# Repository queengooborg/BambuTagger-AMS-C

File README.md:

#  BambuTagger-AMS-C

Multi-spool NFC tag reader for Bambu Lab printers. Reads 4 Bambu Lab filament spool tags via RC522, displays live printer AMS tray data over MQTT, and sends RFID tag data to the printer/BMCU. Fully configurable via web interface with automatic AP fallback and OTA firmware updates.

Supported Tag Formats:

| Tag Type                  | Format            |
| ------------------------- | ----------------- |
| **Bambu Lab**             | MIFARE Classic 1K |
| **SpoolEase**             | NTAG, NDEF URI    |
| **OpenSpool**             | NTAG, NDEF JSON   |
| **OpenTag3D** (v1 and v2) | NTAG, MIME binary |

---

## Features

| Category           | Details                                                                                                         |
| ------------------ | --------------------------------------------------------------------------------------------------------------- |
| **RFID**           | 4x RC522 on shared SPI bus; MIFARE Classic 1K (Bambu Lab) + NTAG (SpoolEase/OpenTag3D/OpenSpool) auto-detection |
| **Key derivation** | HKDF-SHA256 with Bambu Lab salt — no hardcoded keys                                                             |
| **Tag parsers**    | OpenTag3D MIME binary, OpenSpool JSON, SpoolEase NDEF URI, nested NDEF recursion                                |
| **Live AMS sync**  | Reads tray data (material, color, type) from printer over MQTT                                                  |
| **BMCU support**   | Sends `ams_filament_setting` with correct `tray_type`, `tray_color`, `nozzle_temp_min/max`                      |
| **TFT display**    | 240×240 1.3" ST7789VW with boot splash, live AMS tray data, OTA progress, BME280 temp/humidity                  |
| **LEDs**           | 4x WS2812 addressable LEDs with per-slot color from printer AMS tray data                                       |
| **Web UI**         | 3-tab SPA: Status (merged slots + color swatches), Printer Config, WiFi Config                                  |
| **MQTT bridge**    | Subscribes to printer status, publishes `ams_filament_setting` commands                                         |
| **WiFi**           | Auto-STA on boot; AP fallback `192.168.4.1` with captive portal                                                 |
| **OTA updates**    | One-click firmware update from GitHub Releases with TFT progress bar                                            |
| **CI/CD**          | GitHub Actions: build on commit, release on version tags                                                        |

---

## Hardware

This build assumes you have a basic level of microprocessor and breadboard/soldering experience.

### Bill of Materials

There are two options for ESP32 boards: the ESP-WROOM-32 Dev board, or the ESP32-S3-DevKitC-1.

#### ESP-WROOM-32

This is the original board.

| Component            | Required | Notes                                      | Buy/Download/Get                                                                                                                |
| -------------------- | -------- | ------------------------------------------ | ------------------------------------------------------------------------------------------------------------------------------- |
| **ESP32** Dev Module | **Yes**  | Base board                                 | https://de.aliexpress.com/item/1005006589341221.html                                                                            |
| Custom **PCB**       | Optional | DIY PCB from JLPCB (use PCB v1.2 or newer) | https://oshwlab.com/bambutagger/project_hdkkdlsn                                                                                |
| 3D-Printed **Case**  | Optional |                                            | For [AMS](./3d-prints/ESP-WROOM-32/BambuTagger-AMS.3mf)<br /> For [AMS 2 Pro](./3d-prints/ESP-WROOM-32/BambuTagger-AMS2Pro.3mf) |

#### ESP32-S3-DevKitC-1

| Component            | Required | Notes                            | Buy/Download/Get                         |
| -------------------- | -------- | -------------------------------- | ---------------------------------------- |
| **ESP32** Dev Module | **Yes**  | Base board                       |                                          |
| Custom **PCB**       | Optional | DIY PCB designed by @Digitalpunk | [Gerber Files](./PCB/ESP32-S3-DevKitC-1) |

#### Common Components

| Component                           | Required        | Notes                          | Buy/Download/Get                                      |
| ----------------------------------- | --------------- | ------------------------------ | ----------------------------------------------------- |
| **100µF Capacitor**                 | **Yes**         | Regulates power for components |                                                       |
| **4x RC522** RFID/NFC Readers       | **Yes**         | SPI interface, shared bus      | https://de.aliexpress.com/item/1005006233005745.html  |
| **240×240 1.3" TFT**                | **Yes**         | ST7789VW SPI Display           | https://www.aliexpress.com/item/1005007094147766.html |
| **4x WS2812** Addressable LEDs      | Optional        | Daisy-chained, single data pin | https://de.aliexpress.com/item/32560280169.html       |
| **BME280** 3.3V Sensor              | Optional        | Temperature/Humidity, I2C      | https://de.aliexpress.com/item/1005006824236173.html  |
| **4x JST-XH 7-Pin** Connector+Cable | With Custom PCB | For PCB connections to RC522s  |                                                       |

### Wiring / Pin Assignments

If you are not using the custom PCB, you can manually wire all the components.

Connect the ESP32 to a 5V power input, either via the USB port or via the VCC/Vin pin.

The WS2812 LED must also be powered by 5V. If the ESP32 is powered via the USB port, the VCC/Vin pin becomes a 5V output, and can be used to power the LEDs. On some boards, you may need to short two pads (usually labeled VIN->VOUT) via soldering.

Connect the 100µF capacitor from the 3.3V to the ground. This capacitor helps regulate power and prevents back-powering the RC522 readers.

All other components will be powered by the 3.3V pin on the ESP32 board.

| Function                    | ESP-WROOM-32 | ESP32-S3-DevKitC-1 |
| --------------------------- | ------------ | ------------------ |
| **RC522 SPI MOSI (Shared)** | 23           | 11                 |
| **RC522 SPI MISO (Shared)** | 19           | 13                 |
| **RC522 SPI SCK (Shared)**  | 18           | 12                 |
| **RC522 #1 SS (SDA)**       | 13           | 4                  |
| **RC522 #1 RST**            | 26           | 15                 |
| **RC522 #2 SS (SDA)**       | 12           | 5                  |
| **RC522 #2 RST**            | 25           | 16                 |
| **RC522 #3 SS (SDA)**       | 14           | 6                  |
| **RC522 #3 RST**            | 33           | 17                 |
| **RC522 #4 SS (SDA)**       | 27           | 7                  |
| **RC522 #4 RST**            | 32           | 18                 |
| **TFT SDA (MOSI)**          | 17           | 35                 |
| **TFT SCL (SCK)**           | 16           | 36                 |
| **TFT DC**                  | 4            | 37                 |
| **TFT RES**                 | 5            | 0                  |
| **TFT BLK**                 | 2            | 45                 |
| **WS2812 Data**             | 15           | 14                 |
| **BME280 SDA**              | 21           | 48                 |
| **BME280 SCL**              | 22           | 47                 |

---

## Firmware

### Flashing a Release

The easiest way to flash the board firmware is to use a web flashing utility like [ESPFlasher.app](https://espflasher.app/). Simply download the appropriate `firmware_merged.bin` from the [releases](https://github.com/queengooborg/BambuTagger-AMS-C/releases) page and upload it to the flashing utility.

- ESP-WROOM-32 / ESP32 Dev Module - `esp32dev-firmware_merged.bin`
- ESP32-S3-DevKitC-1 - `esp32-s3-devkitc-1-firmware_merged.bin`

Alternatively, if you have `esptool` set up locally, you may run the following command:

- ESP-WROOM-32 / ESP32 Dev Module - `esptool write-flash 0x0 esp32dev-firmware_merged.bin`
- ESP32-S3-DevKitC-1 - `esptool --chip esp32s3 write-flash 0x0 esp32-s3-devkitc-1-firmware_merged.bin`

### Building from Source

To build from source, you may either use Visual Studio Code or run commands in the terminal. The following sections will cover setup for running commands in the terminal.

#### Initial Setup

To setup the local development environment, you can either use Visual Studio Code, or run the `./setup.sh` command. The command will create a Python virtual environment, using the virtualenv manager if one is available, and install dependencies.

> [!NOTE]
> To reactivate the virtualenv at a later time (if you don't have a virtualenv manager), simply run:
>
> ```sh
> source .venv/bin/activate
> ```

#### Build and Upload

```sh
# ESP32-WROOM / ESP32 Dev Module
pio run -e esp32-ams-c
pio run -e esp32-ams-c -t upload

# ESP32-S3-DevKitC-1
pio run -e esp32-s3-devkitc-1
pio run -e esp32-s3-devkitc-1 -t upload
```

---

## How to Use

### Initial Setup

Once the firmware has been flashed for the first time, the ESP32 will initialize and create its own WiFi access point called "BambuTagger-AMS". Connect to the WiFi network to access the web-based configuration panel.

> [!NOTE]
> The configuration panel should automatically appear as a captive portal. If it does not, manually go to it by going to `http://192.168.4.1` in your browser.

Configure your WiFi network first by typing in the SSID name and password, then click "Save WiFi Settings". The ESP32 will reboot automatically. If the network configuration succeeded, you can now switch to your primary WiFi. If it did not, the WiFi access point will reinitialize, allowing you to reconnect.

Once WiFi configuration is completed, reconnect to your device by navigating to `[Device Name].local` (default: `BambuTagger-AMS.local`) or via the IP address displayed on the TFT screen.

Enter in your printer settings on the printer config page, including the IP, serial number and access code.

> [!IMPORTANT]
> Your printer MUST be in LAN Only Mode and Developer Mode. The printer will refuse all connections otherwise.

### Using with Printer

The project is designed with the intent of placing a reader at each AMS slot, similar to how the existing readers are placed. With each reader placed, tag scanning will happen automatically as filament is loaded normally.

--

## Technical Details

### WiFi & Connectivity

#### AP Mode

| Scenario                     | Behavior                                |
| ---------------------------- | --------------------------------------- |
| No WiFi configured           | Opens AP immediately                    |
| WiFi connection fails        | Opens AP after 15 seconds               |
| AP active, credentials exist | Retries STA connection every 30 seconds |
| STA connects while AP active | Closes AP, switches to normal mode      |

**AP Details:**

- **SSID**: Device name (default: `BambuTagger-AMS`)
- **Security**: Open (no password)
- **IP**: `192.168.4.1`
- **Captive portal**: DNS redirects all domains to the config page

#### SSID Mode

When the ESP32 module is connected to an existing network, the IP address will display on the TFT screen. Alternatively, you may navigate to `[Device Name].local` (default: `BambuTagger-AMS.local`).

---

### Web Interface

Open a browser to the ESP32's IP (shown on TFT), `[Device Name].local`, or `http://192.168.4.1` (in AP mode).

| Tab                | Description                                                                                        |
| ------------------ | -------------------------------------------------------------------------------------------------- |
| **Status**         | Merged slot status with AMS data + scanned tag data, color swatches, printer AMS cards, OTA button |
| **Printer Config** | Printer IP, Port (8883), Access Code, Serial Number, AMS Unit selector (A/B/C/D), MQTT settings    |
| **WiFi Config**    | SSID, Password, Device Name                                                                        |

---

### TFT Display (240×240 1.3" ST7789VW)

The TFT display has two modes:

```
┌─────────────────────────────────┐
│ Device Name               WiFi  │  ← status bar (white bg)
├─────────────────────────────────┤
│    1       2                    │
│ ┌─────┐ ┌─────┐ ┌─────┐ ┌─────┐ │  ← color swatch + percentage
│ │  P  │ │     │ │     │ │     │ │
│ │  L  │ │     │ │     │ │     │ │
│ │  A  │ │     │ │     │ │     │ │
│ │     │ │     │ │     │ │     │ │
│ │     │ │     │ │     │ │     │ │
│ └─────┘ └─────┘ └─────┘ └─────┘ │
│                                 │
│  100%                           │
├─────────────────────────────────┤
│ 22C           45%               │  ← temperature, humidity
│ MQTT:OK                  PTR:OK │  ← status line
└─────────────────────────────────┘
```

```
┌─────────────────────────────────┐
│ Device Name               WiFi  │  ← status bar (white bg)
├─────────────────────────────────┤
│ 1: PLA     [■] #C0C0C0FF  100%  │  ← color swatch + percentage
│ 2: empty                        │
│ 3: empty                        │
│ 4: empty                        │
├─────────────────────────────────┤
│ 22C           45%               │  ← temperature, humidity
│ MQTT:OK                  PTR:OK │  ← status line
└─────────────────────────────────┘
```

OTA progress shown on TFT with header/footer preserved:  
"OTA Update" → "Downloading..." → "Flashing... 45%" → auto-reboot

---

### Printer Communication

#### Subscribe

- **Topic**: `device/<serial>/report`
- **Data**: `push_status` (periodic, ~3KB), `get_version` responses

#### Publish

- **Topic**: `device/<serial>/request`

**`ams_filament_setting`** structure:

```json
{
  "print": {
    "sequence_id": "0",
    "command": "ams_filament_setting",
    "ams_id": 0,
    "tray_id": 0,
    "tray_info_idx": "GFA00",
    "tray_color": "RRGGBBFF",
    "nozzle_temp_min": 190,
    "nozzle_temp_max": 230,
    "tray_type": "PLA"
  }
}
```

- `tray_type` derived from filament index prefix (GFA→PLA, GFG→PETG, etc.)
- `tray_color` forced to RRGGBBFF format
- `nozzle_temp_min/max` from tag block 6

---

### Tag Format & Reading

The following tag types are supported:

| Tag Type                  | Format            | Example                                              |
| ------------------------- | ----------------- | ---------------------------------------------------- |
| **Bambu Lab**             | MIFARE Classic 1K | `Bambu - PLA · C12E1FFF · 1000g/1000g`               |
| **SpoolEase**             | NTAG, NDEF URI    | `SpoolEase - PLA · 000000FF · 1000g/1036g`           |
| **OpenSpool**             | NTAG, NDEF JSON   | `OpenSpool - ASA-AF · F078B4FF · 1000g/1000g`        |
| **OpenTag3D** (v1 and v2) | NTAG, MIME binary | `OpenTag3D v2.003 - ASA-AF · F078B4FF · 1000g/1000g` |

#### Bambu Lab (MIFARE Classic 1K)

| Block | Content                                              |
| ----- | ---------------------------------------------------- |
| 0     | UID (4 bytes)                                        |
| 1     | Variant ID + Material index (e.g. "GFA00")           |
| 2     | Filament type short name                             |
| 4     | Detailed type string (e.g. "PLA Basic")              |
| 5     | RGBA color (bytes 0-3) + spool weight LE (bytes 4-5) |
| 6     | Nozzle temps (bytes 8-11 LE)                         |

#### SpoolEase (NTAG, NDEF URI)

URL format: `https://tag.spoolease.io/S1/?TG=...&M=PLA&CC=000000FF&SC=GFL99&WL=1000&WE=179&WF=1215&NN=190&NX=240`

| Param | Field            | Description                         |
| ----- | ---------------- | ----------------------------------- |
| `M=`  | display type     | e.g. "PLA", "PETG"                  |
| `SC=` | `materialType`   | Bambu index for MQTT (e.g. "GFL99") |
| `CC=` | `colorHex`       | RGBA hex (e.g. "000000FF")          |
| `B=`  | `manufacturer`   | Brand name (e.g. "Jayo")            |
| `WL=` | `remainingGrams` | Remaining filament weight           |
| `WE=` | empty spool      | Empty spool weight                  |
| `WF=` | full spool       | `totalGrams = WF - WE`              |
| `NN=` | `nozzleTempMin`  | Min nozzle temp °C                  |
| `NX=` | `nozzleTempMax`  | Max nozzle temp °C                  |

#### OpenTag3D (NTAG, MIME binary)

The OpenTag3D spec can be read on [their website](https://opentag3d.info/spec).

### Authentication & Reading

- **Tag auto-detect**: SAK-based type detection (MIFARE 1K vs NTAG)
- **HKDF-SHA256** derives 16 per-sector Key A/B from 4-byte UID
- Bambu KDF salt/info vectors from reverse-engineered firmware
- Falls back to default key `0xFF...FF` for blank sectors
- Failed auth re-wakes tag via antenna power-cycle
- Dead readers auto-skipped (version register 0x92/0x91/0xB2 check)
- SPI: 1 MHz via `MFRC522_SPI`
- NTAG: page-level reads (page+=4, 4 pages per MIFARE_Read)

### Filament Type Mapping

| Prefix       | Type |
| ------------ | ---- |
| GFA-GFE, GFL | PLA  |
| GFG          | PETG |
| GFH, GFI     | ABS  |
| GFJ          | ASA  |
| GFK          | TPU  |

---

### OTA Updates

- **Button**: "Update Firmware" on Status page (shows "Update to vX.Y.Z" or "up to date")
- **Overlay**: full-screen progress overlay with spinner, status text, progress bar
- **Endpoint**: `POST /api/ota` triggers update, `GET /api/ota-check` checks for newer version
- Downloads latest `.ino.bin` from GitHub Releases, flashes via `Update.h`
- 3 retry attempts with 5s stall detection, fresh HTTP client per attempt
- TFT shows "Checking version..." → "Downloading..." → "Flashing..." with percentage
- Device auto-reboots after successful flash, web UI auto-reloads

---

### Configuration Defaults

| Setting              | Default         |
| -------------------- | --------------- |
| WiFi SSID            | (empty)         |
| WiFi Password        | (empty)         |
| Device Name          | BambuTagger-AMS |
| Printer IP           | 192.168.1.100   |
| Printer Port         | 8883            |
| Access Code          | (empty)         |
| Printer Serial       | (empty)         |
| AMS Unit             | A (0)           |
| MQTT Enabled         | Yes             |
| MQTT TLS             | No              |
| MQTT Update Interval | 3000 ms         |
| RFID Poll Interval   | 100 ms          |
| Firmware Version     | 1.0.8           |

---

## Credits & References

- [RFID-Tag-Guide](https://github.com/Bambu-Research-Group/RFID-Tag-Guide)
- Display library: [Adafruit ST7735/ST7789](https://github.com/adafruit/Adafruit-ST7735-Library)
- RFID library: [MFRC522-spi-i2c-uart-async](https://github.com/miguelbalboa/rfid)
- OpenTag3D spec: [opentag3d.info](https://opentag3d.info)

---

## License

This project is licened under AGPLv3.
This project is provided as-is for personal and educational use.  
Bambu Lab trademarks and spool tag data formats are the property of Bambu Lab.

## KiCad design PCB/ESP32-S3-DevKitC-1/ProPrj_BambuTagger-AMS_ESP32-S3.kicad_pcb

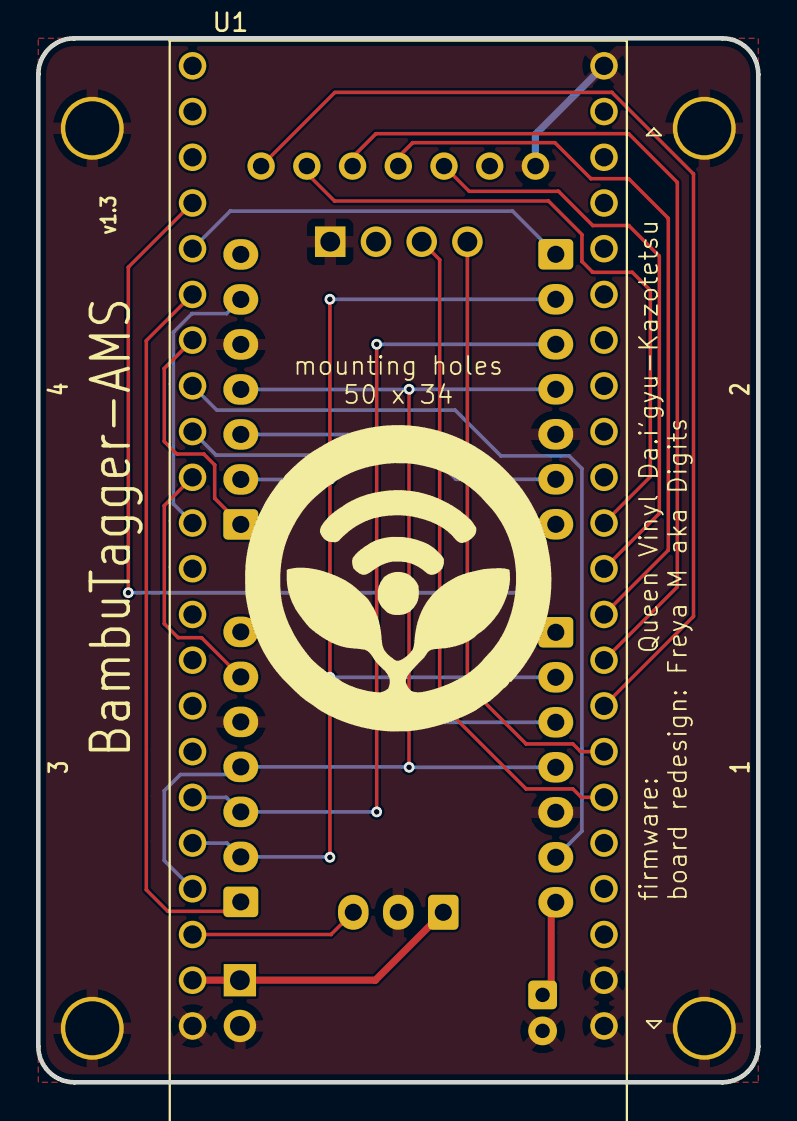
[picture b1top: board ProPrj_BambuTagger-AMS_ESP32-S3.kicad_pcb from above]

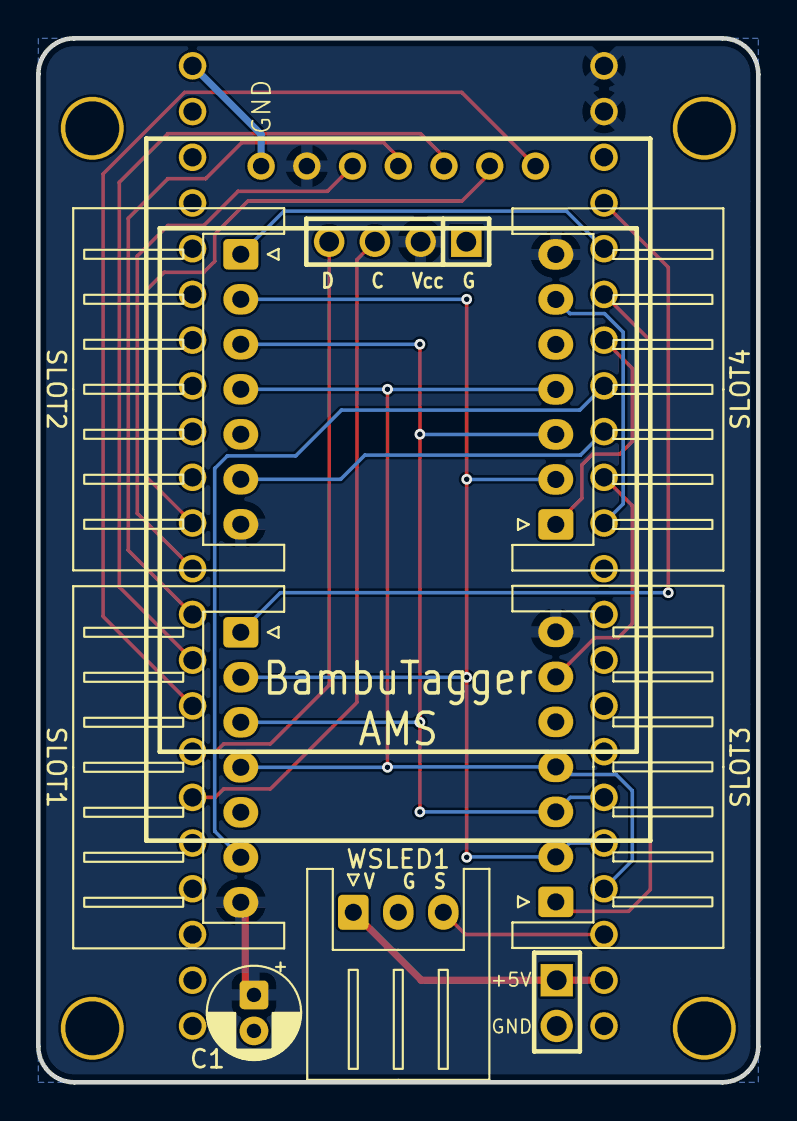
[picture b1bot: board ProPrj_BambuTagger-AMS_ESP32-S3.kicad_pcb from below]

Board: 2 copper layers, 40.0 x 58.0 mm, 10 parts (9 on the bottom side), 22 nets.

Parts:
5V: HDR-TH_2P-P2.54-H-M-W10.4
C1: 100uF; CP_Radial_D5.0mm_P2.00mm
SENSOR: HDR-TH_4P-P2.54-V-M
SLOT1, SLOT2, SLOT3, SLOT4: ZX-XH2.54-7PWZ; JST_XH_S7B-XH-A_1x07_P2.50mm_Horizontal
TFT: 240X240 1.3 TFT SPI DISPLAY
U1: ESP32-S3-DEVKITC-1U-N8R8; MODULE_ESP32-S3-DEVKITC-1U-N8R8
WSLED1: ZX-XH2.54-3PWZ; JST_XH_S3B-XH-A_1x03_P2.50mm_Horizontal

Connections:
3_3V: C1.1, SENSOR.2, SLOT1.7, SLOT2.7, SLOT3.7, SLOT4.7, TFT.6, U1.J1_1 (3V3), U1.J1_2 (3V3)
BLK: TFT.1, U1.J3_15 (GPIO45)
CS1: SLOT1.1, U1.J1_4 (GPIO4)
CS2: SLOT2.1, U1.J1_5 (GPIO5)
CS3: SLOT3.1, U1.J1_6 (GPIO6)
CS4: SLOT4.1, U1.J1_7 (GPIO7)
DC: TFT.2, U1.J3_11 (GPIO37)
GND: 5V.2, C1.2, SENSOR.1, SLOT1.5, SLOT2.5, SLOT3.5, SLOT4.5, TFT.7, U1.J1_22 (GND), U1.J3_1 (GND), U1.J3_21 (GND), U1.J3_22 (GND), WSLED1.2
MISO: SLOT1.4, SLOT2.4, SLOT3.4, SLOT4.4, U1.J1_19 (GPIO13)
MOSI: SLOT1.3, SLOT2.3, SLOT3.3, SLOT4.3, U1.J1_17 (GPIO11)
RES: TFT.3, U1.J3_14 (GPIO0)
RST1: SLOT1.6, U1.J1_8 (GPIO15)
RST2: SLOT2.6, U1.J1_9 (GPIO16)
RST3: SLOT3.6, U1.J1_10 (GPIO17)
RST4: SLOT4.6, U1.J1_11 (GPIO18)
SCK: SLOT1.2, SLOT2.2, SLOT3.2, SLOT4.2, U1.J1_18 (GPIO12)
SCL: SENSOR.3, U1.J3_17 (GPIO47)
SCLTFT: TFT.5, U1.J3_12 (GPIO36)
SDA: SENSOR.4, U1.J3_16 (GPIO48)
SDATFT: TFT.4, U1.J3_13 (GPIO35)
VCC: 5V.1, U1.J1_21 (5V0), WSLED1.1
WSLED: U1.J1_20 (GPIO14), WSLED1.3
